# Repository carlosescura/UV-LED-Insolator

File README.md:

#UV-LED-Insolator#

### UV LED insolator for homemade PCB ###
---------------------------------

  This is a homemade UV-LED insolator aimed to do the "DIY" PCB in home.
  
All you need to build it is:

  1. Two pieces of PCB for the timer and the UV-LED backplate.
  2. An Arduino Mini Pro
  3. Any kind of the popular "16x2" LCD parallel LCD
  4. Some electronics (resistors, pushbuttons, pin headers...)

Let's do it!

More info: [Carlitosspedia](http://www.carlitosspedia.info)

[www.carlitosspedia.info](http://www.carlitosspedia.info)

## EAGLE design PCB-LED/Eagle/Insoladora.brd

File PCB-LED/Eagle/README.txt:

This homemade insolator is designed for a 165x125mm single side board or more.

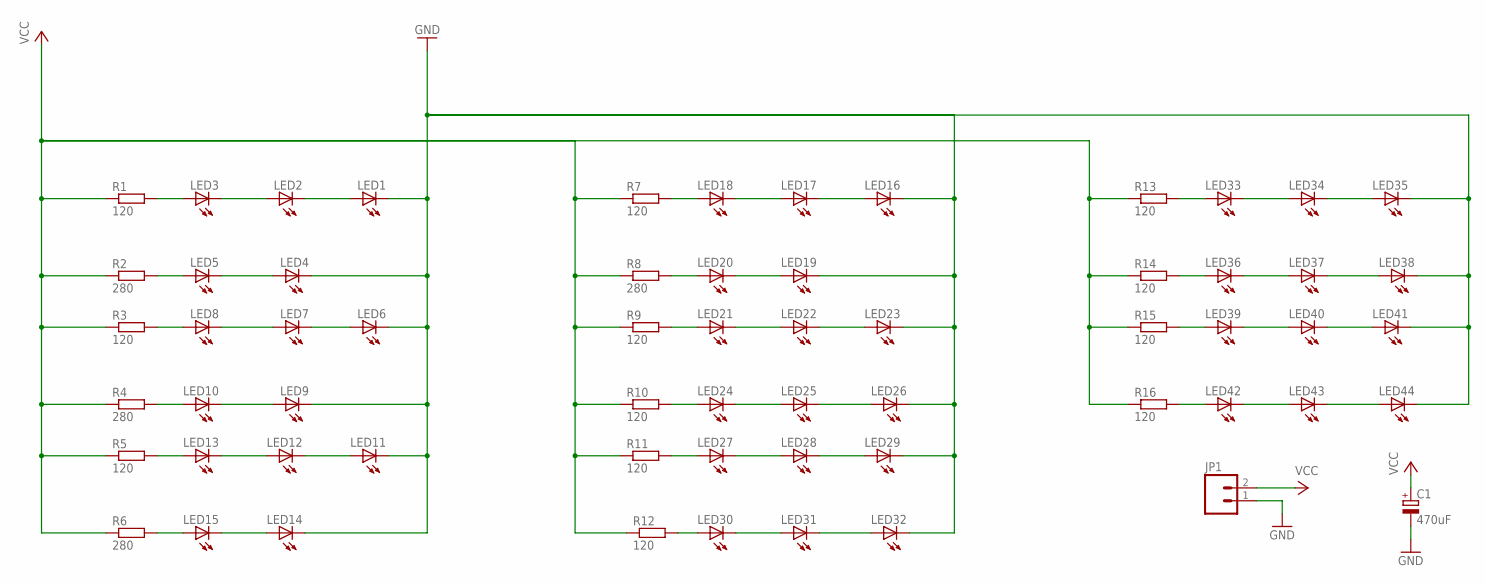
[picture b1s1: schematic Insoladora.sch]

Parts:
C1: 470uF; E2,5-7
JP1: M023.5MM_LOCK; SCREWTERMINAL-3.5MM-2_LOCK
LED1, LED2, LED3, LED4, LED5, LED6, LED7, LED8, LED9, LED10, LED11, LED12, LED13, LED14, LED15, LED16, LED17, LED18, LED19, LED20, LED21, LED22, LED23, LED24, LED25, LED26, LED27, LED28, LED29, LED30, LED31, LED32, LED33, LED34, LED35, LED36, LED37, LED38, LED39, LED40, LED41, LED42, LED43, LED44: LED5MM
R1, R3, R5, R7, R9, R10, R11, R12, R13, R14, R15, R16: 120; 0207/10
R2, R4, R6, R8: 280; 0207/10

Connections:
GND: C1.-, JP1.1, LED1.K (C), LED4.K (C), LED6.K (C), LED9.K (C), LED11.K (C), LED14.K (C), LED16.K (C), LED19.K (C), LED23.K (C), LED26.K (C), LED29.K (C), LED32.K (C), LED35.K (C), LED38.K (C), LED41.K (C), LED44.K (C)
unnamed: LED3.A, R1.2
unnamed: LED2.A, LED3.K (C)
unnamed: LED1.A, LED2.K (C)
unnamed: LED5.A, R2.2
unnamed: LED4.A, LED5.K (C)
unnamed: LED8.A, R3.2
unnamed: LED7.A, LED8.K (C)
unnamed: LED21.A, R9.2
unnamed: LED6.A, LED7.K (C)
unnamed: LED24.A, R10.2
unnamed: LED10.A, R4.2
unnamed: LED9.A, LED10.K (C)
unnamed: LED30.A, R12.2
unnamed: LED13.A, R5.2
unnamed: LED42.A, R16.2
unnamed: LED21.K (C), LED22.A
unnamed: LED22.K (C), LED23.A
unnamed: LED33.A, R13.2
unnamed: LED18.A, R7.2
unnamed: LED12.A, LED13.K (C)
unnamed: LED17.A, LED18.K (C)
unnamed: LED16.A, LED17.K (C)
unnamed: LED11.A, LED12.K (C)
unnamed: LED24.K (C), LED25.A
unnamed: LED25.K (C), LED26.A
unnamed: LED15.A, R6.2
unnamed: LED27.K (C), LED28.A
unnamed: LED28.K (C), LED29.A
unnamed: LED14.A, LED15.K (C)
unnamed: LED30.K (C), LED31.A
unnamed: LED31.K (C), LED32.A
unnamed: LED20.A, R8.2
unnamed: LED33.K (C), LED34.A
unnamed: LED34.K (C), LED35.A
unnamed: LED19.A, LED20.K (C)
unnamed: LED36.K (C), LED37.A
unnamed: LED37.K (C), LED38.A
unnamed: LED39.K (C), LED40.A
unnamed: LED40.K (C), LED41.A
unnamed: LED42.K (C), LED43.A
unnamed: LED43.K (C), LED44.A
unnamed: LED27.A, R11.2
unnamed: LED36.A, R14.2
unnamed: LED39.A, R15.2
VCC: C1.+, JP1.2, R1.1, R2.1, R3.1, R4.1, R5.1, R6.1, R7.1, R8.1, R9.1, R10.1, R11.1, R12.1, R13.1, R14.1, R15.1, R16.1

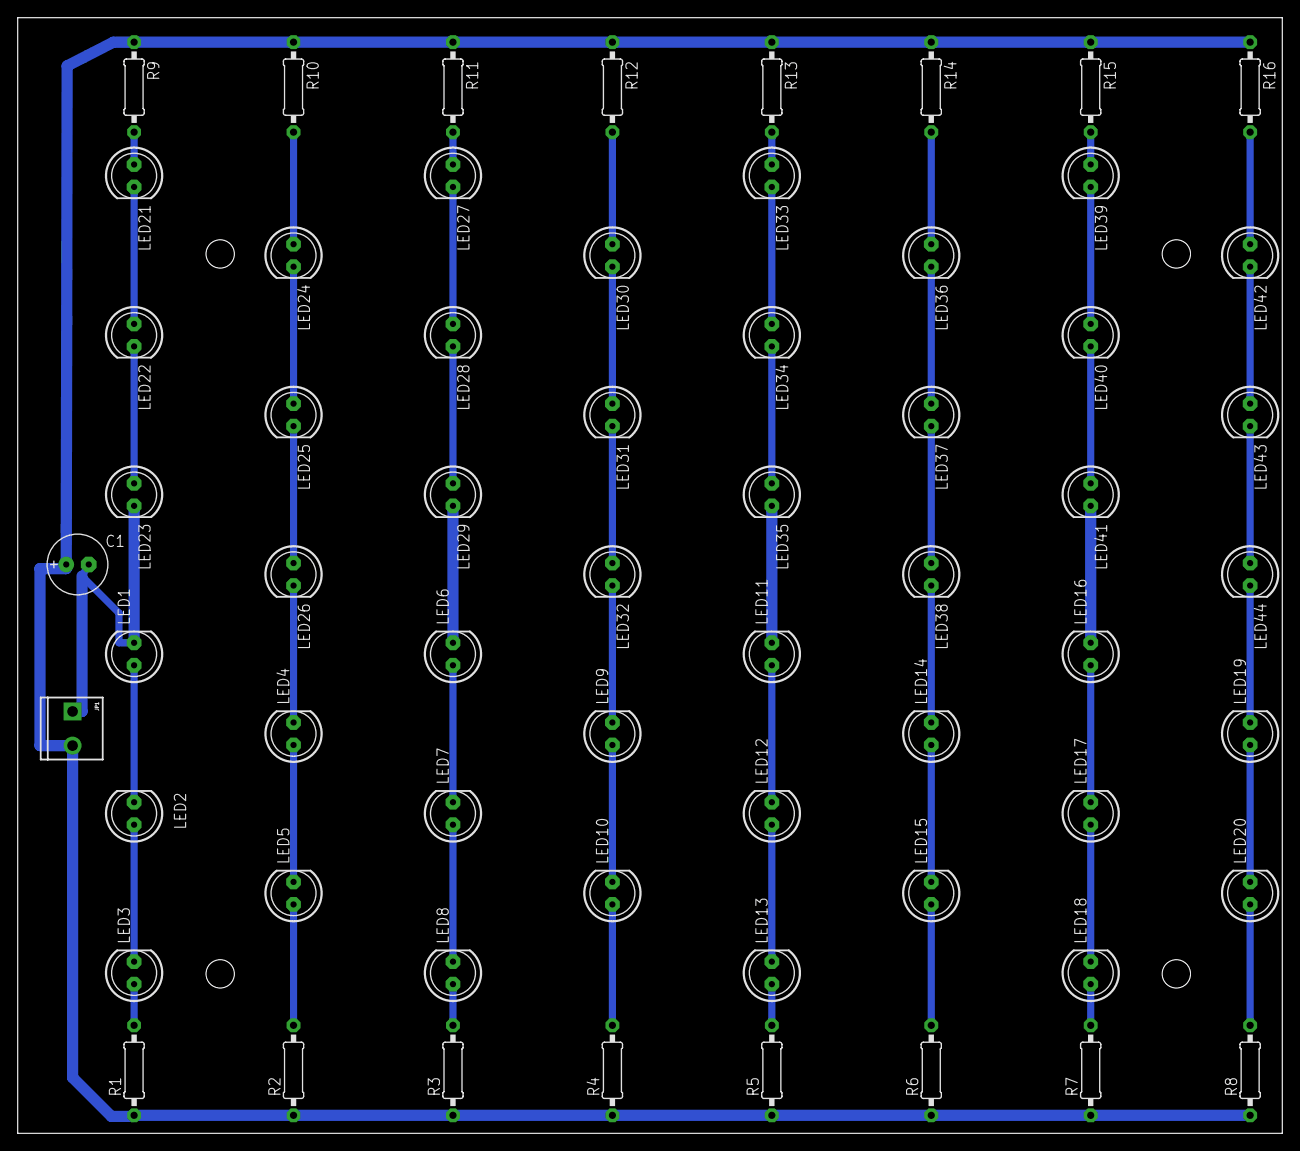
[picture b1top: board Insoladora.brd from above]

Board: 2 copper layers, 142.8 x 126.0 mm, 62 parts (0 on the bottom side), 46 nets.

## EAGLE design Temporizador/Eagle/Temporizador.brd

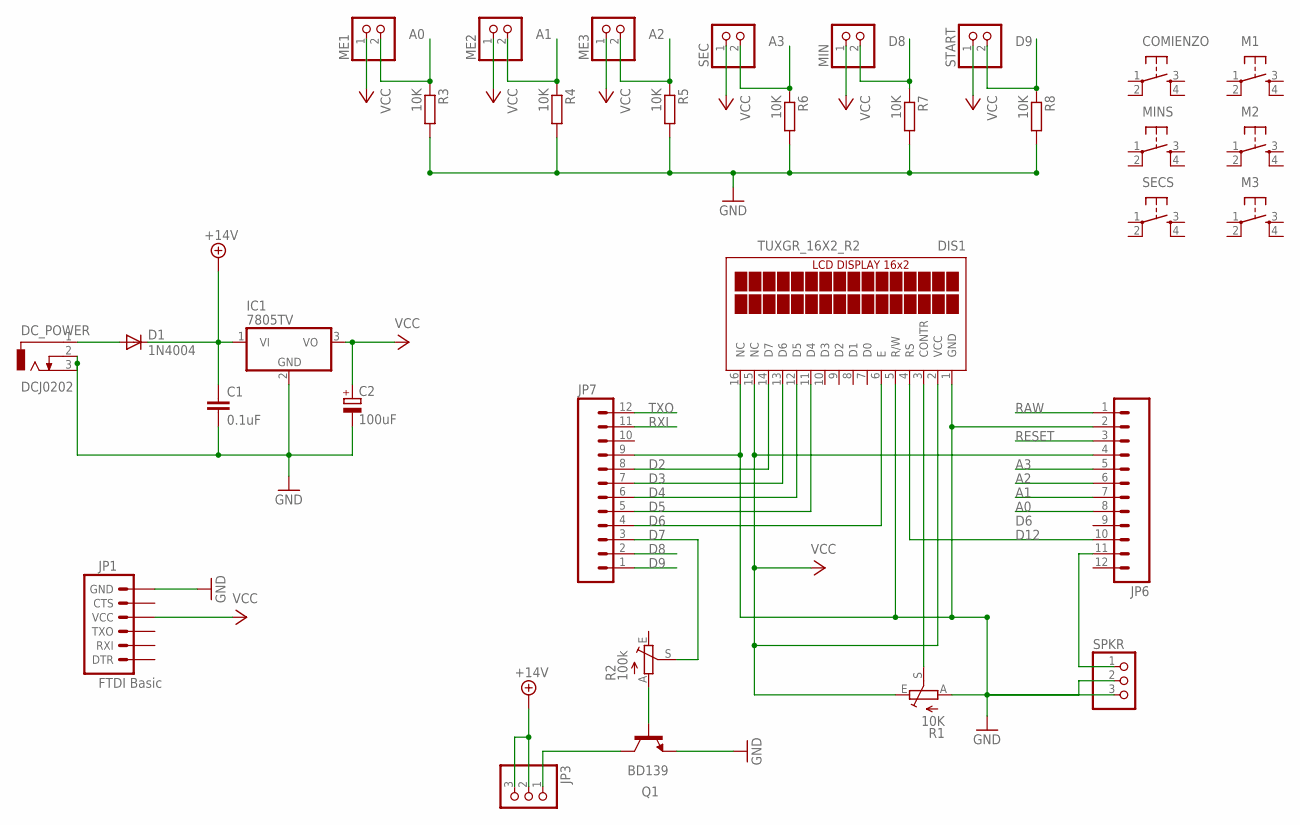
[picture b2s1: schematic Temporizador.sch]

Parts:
C1: 0.1uF; C025-030X050
C2: 100uF; E2,5-7
COMIENZO: TAC_SWITCHPTH; TACTILE-PTH
D1: 1N4004; DO41-10
DC_POWER: DCJ0202
DIS1: TUXGR_16X2_R2
IC1: 7805TV; TO220V
JP1: FTDI Basic; 1X06
JP3: PINHD-1X3; 1X03
JP6, JP7: M12LONGPADS; 1X12_LONGPADS
M1, M2, M3: TAC_SWITCHPTH; TACTILE-PTH
ME1, ME2, ME3: PINHD-1X2; 1X02
MIN: PINHD-1X2; 1X02
MINS: TAC_SWITCHPTH; TACTILE-PTH
Q1: BD139; TO126
R1: 10K; CA6V
R2: 100k; CA6V
R3, R4, R5, R6, R7, R8: 10K; 0309/12
SEC: PINHD-1X2; 1X02
SECS: TAC_SWITCHPTH; TACTILE-PTH
SPKR: PINHD-1X3; 1X03
START: PINHD-1X2; 1X02

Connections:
+14V: C1.1, D1.C, IC1.1 (VI), JP3.2, JP3.3
A0: JP6.8, ME1.2, R3.1
A1: JP6.7, ME2.2, R4.1
A2: JP6.6, ME3.2, R5.1
A3: JP6.5, R6.1, SEC.2
D2: DIS1.14 (D7), JP7.8
D3: DIS1.13 (D6), JP7.7
D4: DIS1.12 (D5), JP7.6
D5: DIS1.11 (D4), JP7.5
D6: DIS1.6 (E), JP7.4
D7: JP7.3, R2.S
D8: JP7.2, MIN.2, R7.1
D9: JP7.1, R8.1, START.2
D12: DIS1.4 (RS), JP6.10
GND: C1.2, C2.-, DC_POWER.2, DC_POWER.3, DIS1.1 (GND), DIS1.5 (R/W), DIS1.16 (NC), IC1.2 (GND), JP1.6 (GND), JP6.2, JP7.9, Q1.1 (E), R1.A, R3.2, R4.2, R5.2, R6.2, R7.2, R8.2, SPKR.2, SPKR.3
unnamed: DIS1.3 (CONTR), R1.S
unnamed: JP6.11, SPKR.1
unnamed: Q1.3 (B), R2.A
unnamed: JP3.1, Q1.2 (C)
unnamed: D1.A, DC_POWER.1
RAW: JP6.1
RESET: JP6.3
RXI: JP7.11
TXO: JP7.12
VCC: C2.+, DIS1.2 (VCC), DIS1.15 (NC), IC1.3 (VO), JP1.4 (VCC), JP6.4, ME1.1, ME2.1, ME3.1, MIN.1, R1.E, SEC.1, START.1

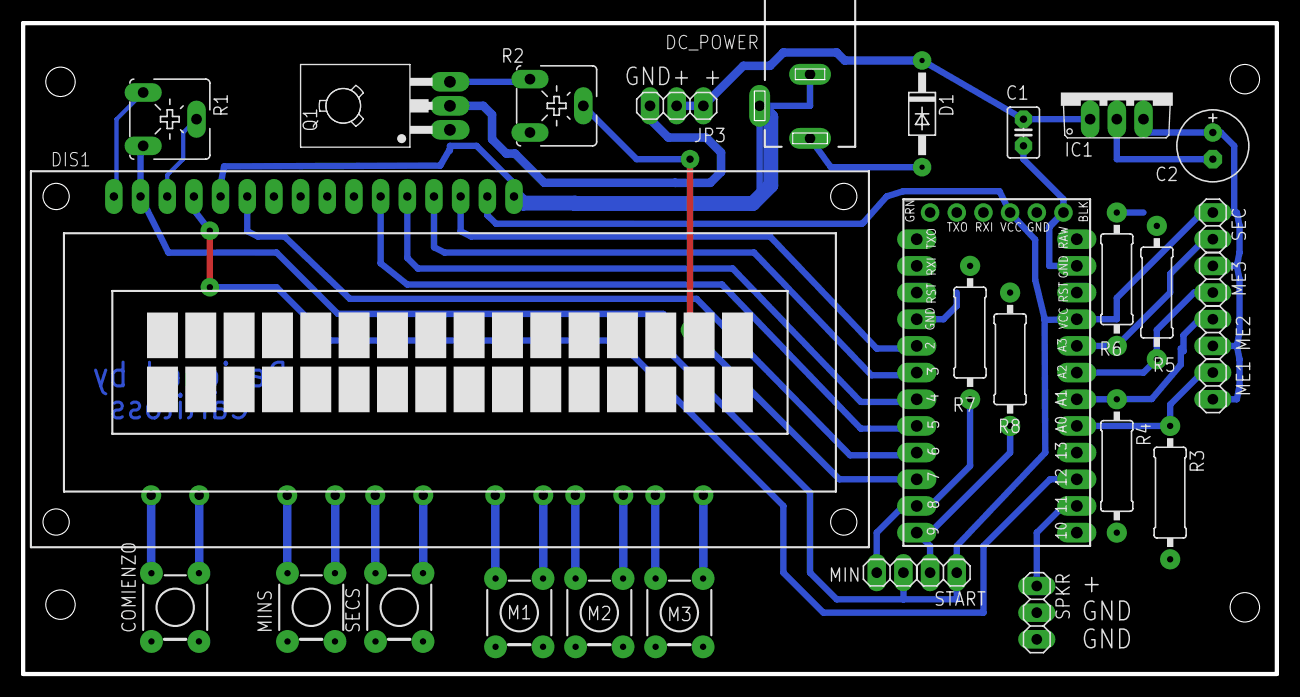
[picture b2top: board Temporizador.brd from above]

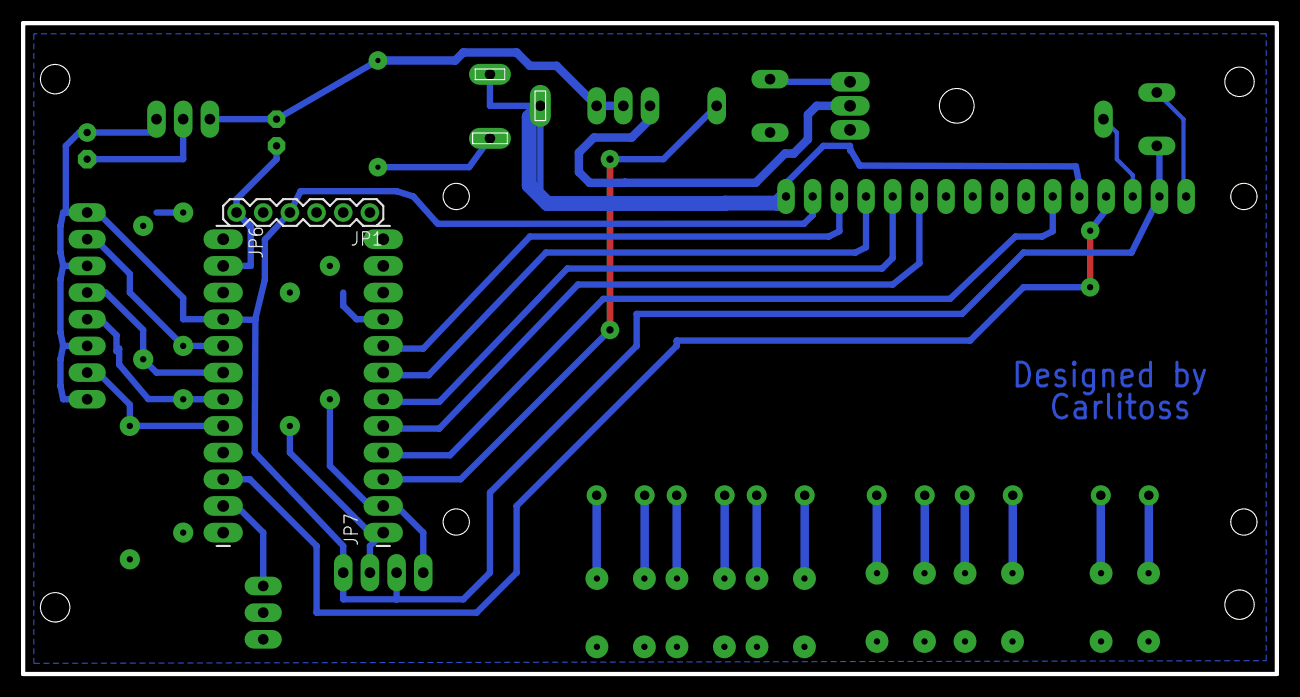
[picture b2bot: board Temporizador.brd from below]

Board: 2 copper layers, 119.4 x 62.0 mm, 32 parts (3 on the bottom side), 21 nets.

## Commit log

2013-04-15 PCB ver 1.0
    First version of the PCB insolator
2013-05-02 Added timer to the project
    Added a timer to the project with LCD based on Arduino Pro mini
2013-05-03 README UPDATED
2013-05-16 Board v1.2
    Added more useful pins, comments and larger pads for better soldering
2013-05-20 Board v1.3
    Added new power supply connector and bigger pads for ease soldering

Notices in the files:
parts and their libraries:
SparkFun-Connectors: Licensing: CC v3.0 Share-Alike You are welcome to use this library for commercial purposes.
